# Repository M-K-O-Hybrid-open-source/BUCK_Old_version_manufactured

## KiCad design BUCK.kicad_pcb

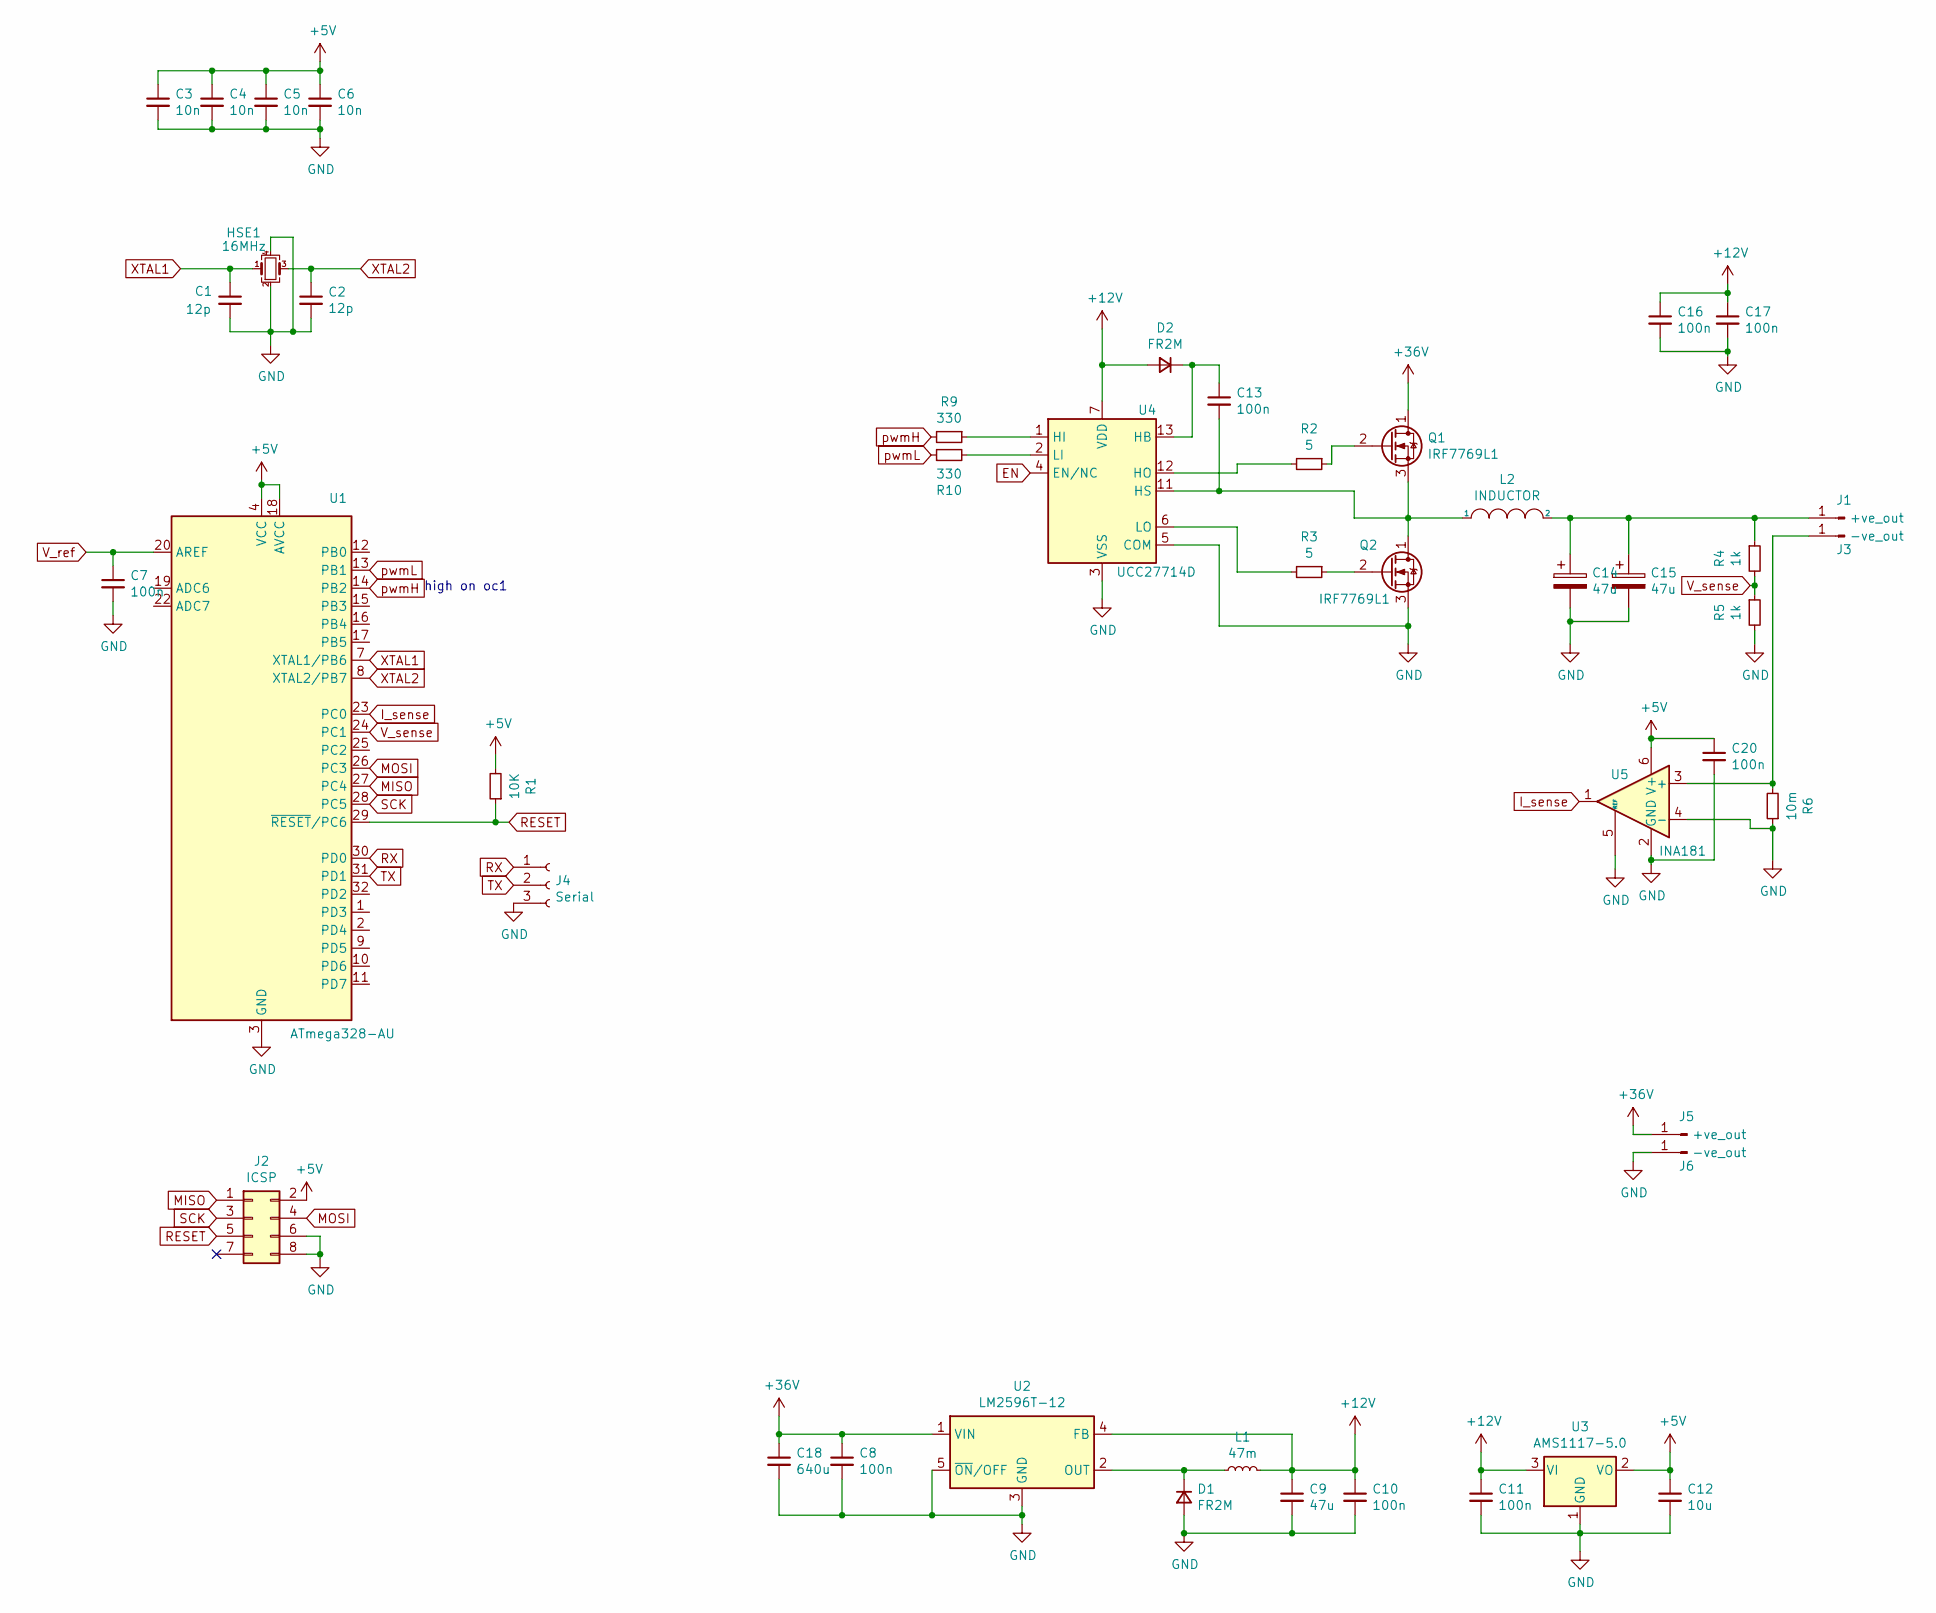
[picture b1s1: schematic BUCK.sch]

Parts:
C1, C2: 12p; C_0805_2012Metric
C3, C4, C5, C6: 10n; C_0805_2012Metric
C7, C8, C10, C11, C13, C16, C17, C20: 100n; C_0805_2012Metric
C9: 47u; C_0805_2012Metric
C12: 10u; C_0805_2012Metric
C14, C15: 47u; CP_Elec_6.3x7.7
C18: 640u; C_0805_2012Metric
D1, D2: FR2M; D_SMB
HSE1: 16MHz; Crystal_SMD_3225-4Pin_3.2x2.5mm
J1, J5: +ve_out; SolderWirePad_1x01_SMD_1x2mm
J2: ICSP; PinSocket_2x04_P2.54mm_Vertical
J3, J6: -ve_out; SolderWirePad_1x01_SMD_1x2mm
J4: Serial; PinHeader_1x03_P2.54mm_Vertical
L1: 47m; L_Sunlord_MWSA0518_5.4x5.2mm
L2: INDUCTOR; L_Toroid_Vertical_L16.8mm_W9.2mm_P7.10mm_Vishay_TJ3
Q1, Q2: IRF7769L1; DirectFET_L8
R1: 10K; R_0805_2012Metric
R2, R3: 5; R_0805_2012Metric
R4, R5: 1k; R_0805_2012Metric
R6: 10m; R_2512_6332Metric
R9, R10: 330; R_0805_2012Metric
U1: ATmega328-AU; TQFP-32_7x7mm_P0.8mm
U2: LM2596T-12; TO-220-5_Vertical
U3: AMS1117-5.0; SOT-223-3_TabPin2
U4: UCC27714D; SOIC-14_3.9x8.7mm_P1.27mm
U5: INA181; SOT-23-6

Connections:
+5V: C3.1, C4.1, C5.1, C6.1, C12.1, C20.1, J2.2, R1.2, U1.4 (VCC), U1.6 (VCC), U1.18 (AVCC), U3.2 (VO), U5.6 (V+)
+12V: C9.1, C10.1, C11.1, C16.1, C17.1, D2.2 (A), L1.2, U2.4 (FB), U3.3 (VI), U4.7 (VDD)
+36V: C8.1, C18.1, J5.1, Q1.1 (D), U2.1 (VIN)
EN: U4.4 (EN/NC)
GND: C1.2, C2.2, C3.2, C4.2, C5.2, C6.2, C7.2, C8.2, C9.2, C10.2, C11.2, C12.2, C14.2, C15.2, C16.2, C17.2, C18.2, C20.2, D1.2 (A), HSE1.2, HSE1.4, J2.6, J2.8, J4.3, J6.1, Q2.3 (S), R5.2, R6.1, U1.3 (GND), U1.5 (GND), U1.21 (GND), U2.3 (GND), U2.5 (~ON~/OFF), U3.1 (GND), U4.3 (VSS), U4.5 (COM), U5.2 (GND), U5.4 (-), U5.5 (REF)
I_sense: U1.23 (PC0), U5.1
MISO: J2.1, U1.27 (PC4)
MOSI: J2.4, U1.26 (PC3)
unnamed: C13.1, D2.1 (K), U4.13 (HB)
unnamed: C13.2, L2.1, Q1.3 (S), Q2.1 (D), U4.11 (HS)
unnamed: C14.1, C15.1, J1.1, L2.2, R4.1
unnamed: D1.1 (K), L1.1, U2.2 (OUT)
unnamed: J3.1, R6.2, U5.3 (+)
unnamed: Q1.2 (G), R2.1
unnamed: Q2.2 (G), R3.1
unnamed: R2.2, U4.12 (HO)
unnamed: R3.2, U4.6 (LO)
unnamed: R9.1, U4.1 (HI)
unnamed: R10.2, U4.2 (LI)
RESET: J2.5, R1.1, U1.29 (~RESET~/PC6)
RX: J4.1, U1.30 (PD0)
SCK: J2.3, U1.28 (PC5)
TX: J4.2, U1.31 (PD1)
V_ref: C7.1, U1.20 (AREF)
V_sense: R4.2, R5.1, U1.24 (PC1)
XTAL1: C1.1, HSE1.1, U1.7 (XTAL1/PB6)
XTAL2: C2.1, HSE1.3, U1.8 (XTAL2/PB7)
pwmH: R9.2, U1.14 (PB2)
pwmL: R10.1, U1.13 (PB1)

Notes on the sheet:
high on oc1

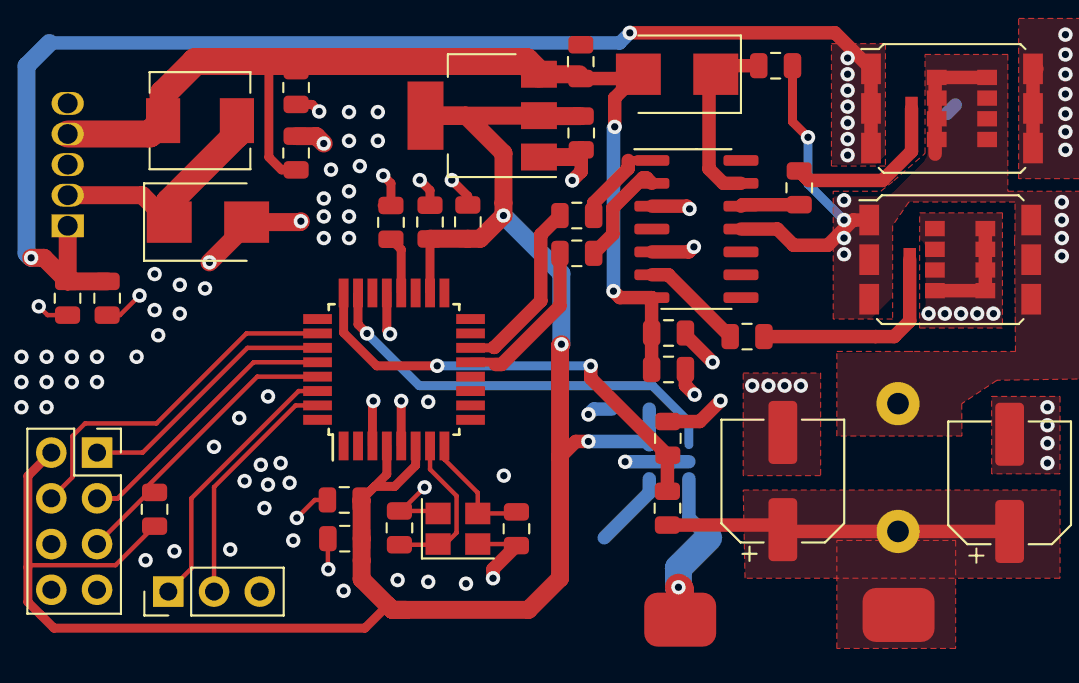
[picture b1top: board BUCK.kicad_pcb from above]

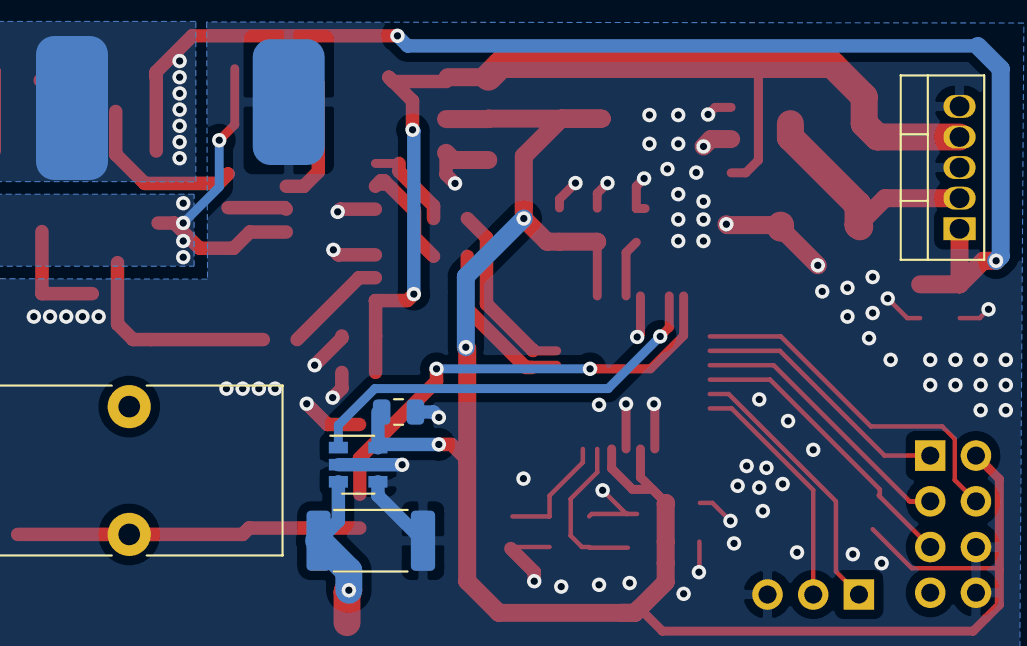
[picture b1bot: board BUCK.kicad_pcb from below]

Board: 2 copper layers, 45 parts (7 on the bottom side), 28 nets.
